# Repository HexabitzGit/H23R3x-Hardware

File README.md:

# H23R3x-Hardware
Hexabitz BlueNRG-M2 Bluetooth Module Hardware Design

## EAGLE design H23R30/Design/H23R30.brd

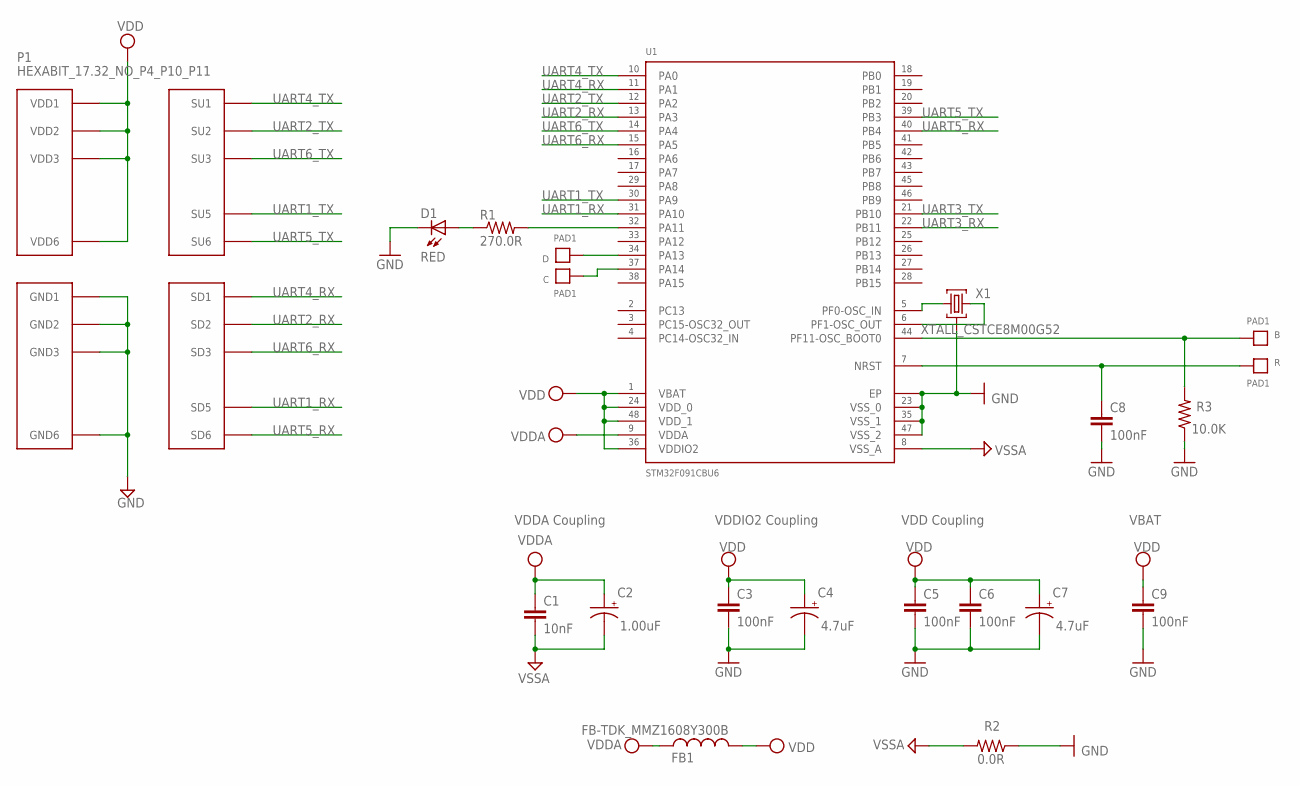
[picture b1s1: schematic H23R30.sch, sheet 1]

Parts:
B: PAD1
C: PAD1
C1: 10nF; C-0603; TOLERANCE 10%; VOLTAGE_RATING 50V; MPN C0603C103K5RACTU
C2: 1.00uF; C-0805-POL; TOLERANCE 10%; VOLTAGE_RATING 16V; MPN CC0805KKX7R7BB105
C3, C6, C8: 100nF; C-0603; TOLERANCE 10%; VOLTAGE_RATING 10V; MPN C0603C104K8RACTU
C4, C7: 4.7uF; C-0805-POL; TOLERANCE 10%; VOLTAGE_RATING 25V; MPN GRM21BC81E475KA12L
C5: 100nF; C-0603; TOLERANCE 10%; VOLTAGE_RATING 10; MPN C0603C104K8RACTU
C9: 100nF; C-0603; TOLERANCE 10V; VOLTAGE_RATING 10%; MPN C0603C104K8RACTU
D: PAD1
D1: RED; VLMS1300-GS08; MPN VLMS1300-GS08
FB1: FB-TDK_MMZ1608Y300B; MPN MMZ1608Y300B
P1: HEXABIT_17.32_NO_P4_P10_P11
R: PAD1
R1: 270.0R; R-0603; TOLERANCE 1%; MPN RC0603FR-07270RL
R2: 0.0R; R-0603; MPN RC0603JR-070RL
R3: 10.0K; R-0603; TOLERANCE 5%; MPN RC0603JR-0710KL
U1: STM32F091CBU6
X1: XTALL_CSTCE8M00G52

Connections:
B1: B.P$1, B.P$2, R3.2, U1.P$44 (PF11-OSC_BOOT0)
GND: C3.2, C4.2 (-), C5.2, C6.2, C7.2 (-), C8.2, C9.2, D1.C, P1.PAD_PD7 (GND1), P1.PAD_PD8 (GND2), P1.PAD_PD9 (GND3), P1.PAD_PD12 (GND6), R2.1, R3.1, U1.EP, U1.P$23 (VSS_0), U1.P$35 (VSS_1), U1.P$47 (VSS_2), X1.P$2 (2); also elsewhere on the board
unnamed: R1.2, U1.P$32 (PA11)
unnamed: D1.A, R1.1
unnamed: U1.P$5 (PF0-OSC_IN), X1.P$1 (1)
unnamed: U1.P$6 (PF1-OSC_OUT), X1.P$3 (3)
unnamed: D.P$1, D.P$2, U1.P$34 (PA13)
unnamed: C.P$1, C.P$2, U1.P$37 (PA14)
R1: C8.1, R.P$1, R.P$2, U1.P$7 (NRST)
UART1_RX: P1.PAD_PD5 (SD5), U1.P$31 (PA10)
UART1_TX: P1.PAD_PU5 (SU5), U1.P$30 (PA9)
UART2_RX: P1.PAD_PD2 (SD2), U1.P$13 (PA3)
UART2_TX: P1.PAD_PU2 (SU2), U1.P$12 (PA2)
UART3_RX: U1.P$22 (PB11); also elsewhere on the board
UART3_TX: U1.P$21 (PB10); also elsewhere on the board
UART4_RX: P1.PAD_PD1 (SD1), U1.P$11 (PA1)
UART4_TX: P1.PAD_PU1 (SU1), U1.P$10 (PA0)
UART5_RX: P1.PAD_PD6 (SD6), U1.P$40 (PB4)
UART5_TX: P1.PAD_PU6 (SU6), U1.P$39 (PB3)
UART6_RX: P1.PAD_PD3 (SD3), U1.P$15 (PA5)
UART6_TX: P1.PAD_PU3 (SU3), U1.P$14 (PA4)
VDD: C3.1, C4.1 (+), C5.1, C6.1, C7.1 (+), C9.1, FB1.2, P1.PAD_PU7 (VDD1), P1.PAD_PU8 (VDD2), P1.PAD_PU9 (VDD3), P1.PAD_PU12 (VDD6), U1.P$1 (VBAT), U1.P$24 (VDD_0), U1.P$36 (VDDIO2), U1.P$48 (VDD_1); also elsewhere on the board
VDDA: C1.1, C2.1 (+), FB1.1, U1.P$9 (VDDA)
VSSA: C1.2, C2.2 (-), R2.2, U1.P$8 (VSS_A)

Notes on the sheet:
VDDA Coupling
VDDIO2 Coupling
VDD Coupling
VBAT

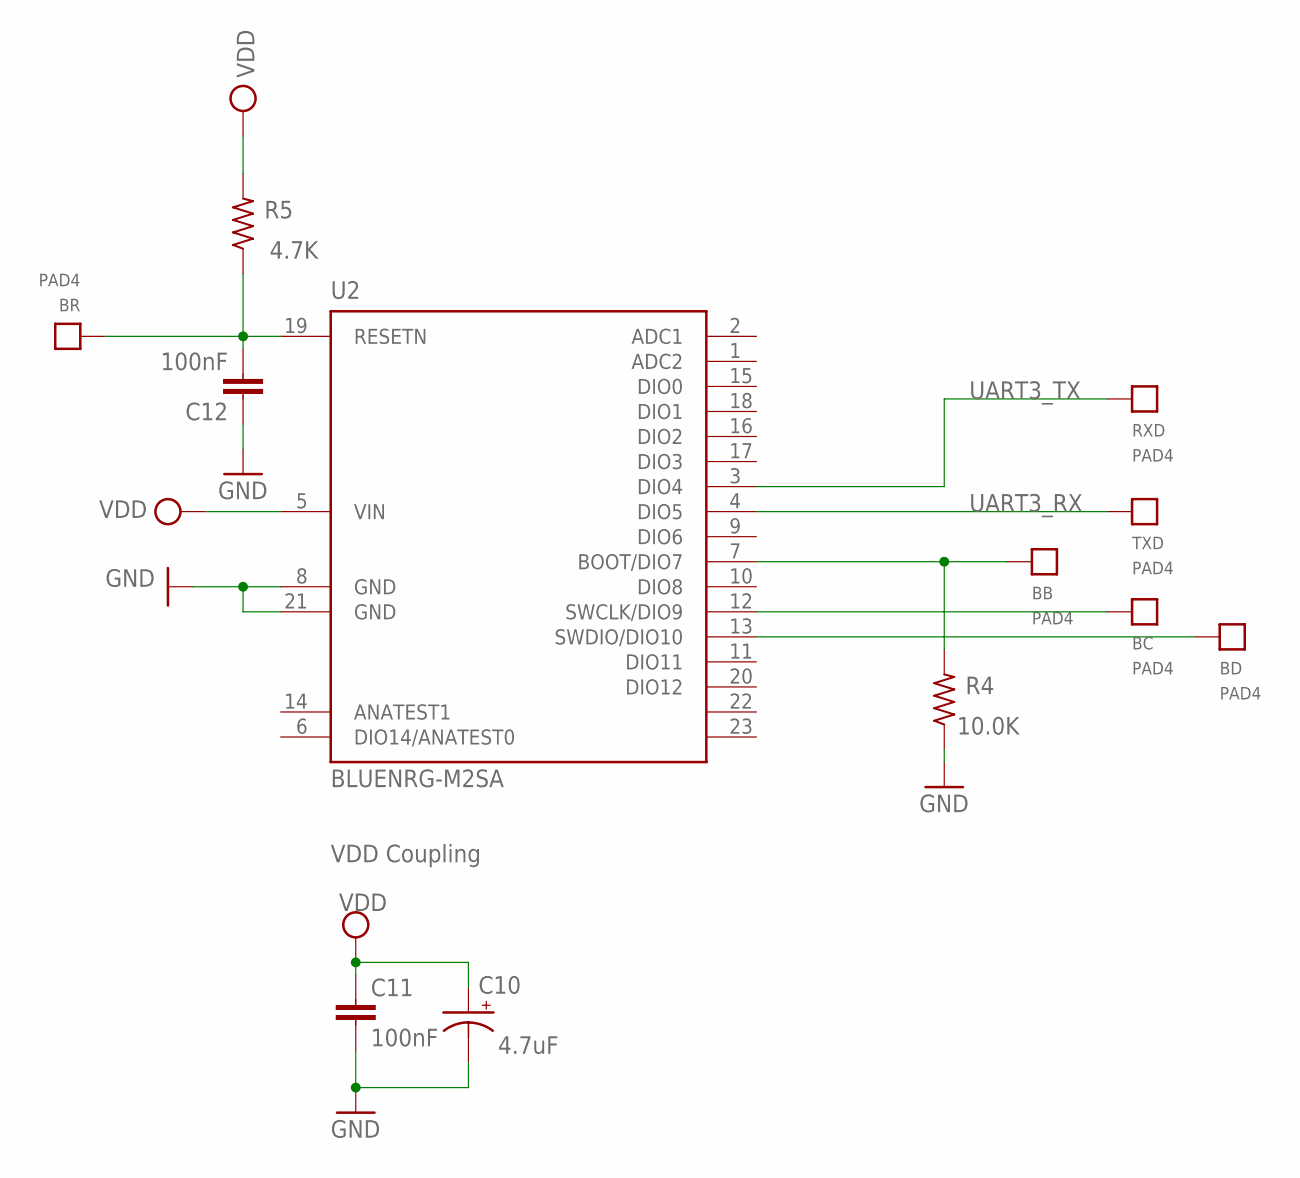
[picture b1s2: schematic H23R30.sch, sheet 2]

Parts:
BB: PAD4
BC: PAD4
BD: PAD4
BR: PAD4
C10: 4.7uF; C-0805-POL; TOLERANCE 10%; VOLTAGE_RATING 25V; MPN GRM21BC81E475KA12L
C11, C12: 100nF; C-0603; TOLERANCE 10%; VOLTAGE_RATING 10; MPN C0603C104K8RACTU
R4: 10.0K; R-0603; TOLERANCE 5%; MPN RC0603JR-0710KL
R5: 4.7K; R-0603; TOLERANCE 5%; MPN RC0603JR-074K7L
RXD: PAD4
TXD: PAD4
U2: BLUENRG-M2SA; BLURNGR-M2SA_FOOTPRINT

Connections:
B2: BB.P$1, R4.2, U2.7 (BOOT/DIO7)
GND: C10.2 (-), C11.2, C12.1, R4.1, U2.8 (GND), U2.21 (GND); also elsewhere on the board
unnamed: BD.P$1, U2.13 (SWDIO/DIO10)
unnamed: BC.P$1, U2.12 (SWCLK/DIO9)
unnamed: BR.P$1, C12.2, R5.1, U2.19 (RESETN)
UART3_RX: TXD.P$1, U2.4 (DIO5); also elsewhere on the board
UART3_TX: RXD.P$1, U2.3 (DIO4); also elsewhere on the board
VDD: C10.1 (+), C11.1, R5.2, U2.5 (VIN); also elsewhere on the board

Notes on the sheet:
VDD Coupling

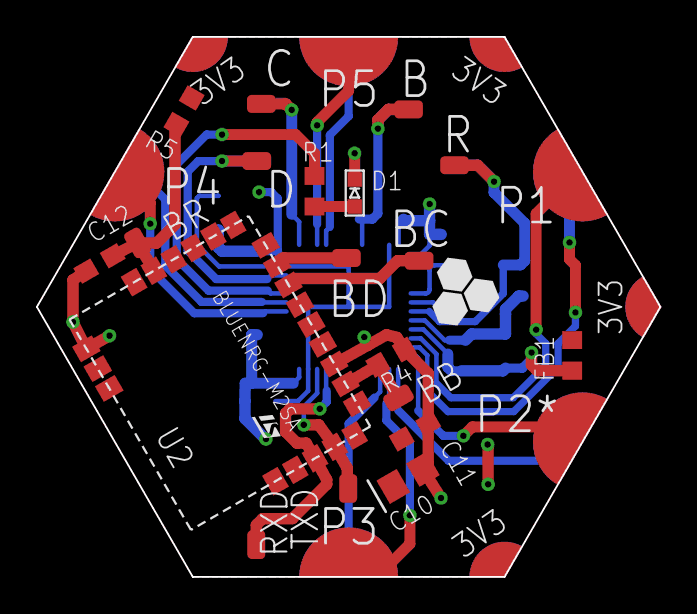
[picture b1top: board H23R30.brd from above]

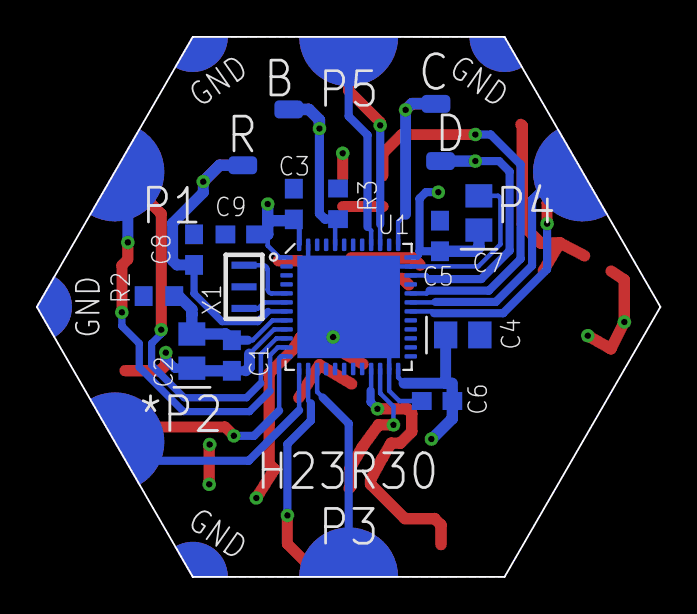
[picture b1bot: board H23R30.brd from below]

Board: 2 copper layers, 34.6 x 30.0 mm, 33 parts (13 on the bottom side), 28 nets.

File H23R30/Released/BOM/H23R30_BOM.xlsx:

Qty | Value | Designator | Description | CAPACITANCE | MFN | MPN | OCTOPART_URL | TOLERANCE
1 | 0.0R | R2 | Thick Film Resistors - SMD 0603 |  | Yageo | RC0603JR-070RL | https://octopart.com/rc0603jr-070rl-yageo-1241539?r=sp&s=X2N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
1 | 270.0R | R1 | Thick Film Resistors - SMD 0603 |  | Yageo | RC0603FR-07270RL | https://octopart.com/search?q=RC0603FR-07270RL&start=0 | 0.01
1 | 4.7K | R5 | Thick Film Resistors - SMD 0603 |  | Yageo | RC0603JR-074K7L | https://octopart.com/rc0603jr-074k7l-yageo-55458509?r=sp | 0.05
2 | 10.0K | R3, R4 | Thick Film Resistors - SMD 0603 |  | Yageo | RC0603JR-0710KL | https://octopart.com/search?q=RC0603JR-0710KL&start=0 | 0.05
1 | 10nF | C1 | CAP CER 10% X7R 0603 | 10nF | KEMET | C0603C103K5RACTU | https://octopart.com/c0603c103k5ractu-kemet-133094?r=sp&s=R_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 | 0.1
7 | 100nF | C5, C11, C12, C3, C6, C8, C9 | CAP CER 10% X7R 0603 | 100nF | KEMET | C0603C104K8RACTU | https://octopart.com/c0603c104k8ractu-kemet-145075?r=sp&s=9b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 | 0.1
1 | 1.00uF | C2 | Cap Tant Solid SMD 2012 | 1.00uF | Yageo | CC0805KKX7R7BB105 | https://octopart.com/cc0805kkx7r7bb105-yageo-8376555?r=sp&s=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 | 0.1
3 | 4.7uF | C4, C7, C10 | Cap Tant Solid SMD 2012 | 4.7uF | Murata | GRM21BC81E475KA12L | https://octopart.com/grm21bc81e475ka12l-murata-10331911?r=sp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 | 0.1
1 | BLUENRG-M2SA | U2 | Embedded ST BlueNRG-2 BLE SoC |  | STMicroelectronics | BlueNRG_M2SA | https://octopart.com/bluenrg-m2sa-stmicroelectronics-104772812?r=sp
1 | FB-TDK_MMZ1608Y300B | FB1 | Ferrite Beads Multi-Layer 30Ohm 25% 100MHz 1.5A 50mOhm DCR 0603 |  | TDK | MMZ1608Y300B | https://octopart.com/mmz1608y300b-tdk-368280?r=sp&s=cd9_2ZEq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
4 | PAD1 | B, C, D, R
6 | PAD4 | BB, BC, BD, BR, RXD, TXD
1 | RED | D1 | Red 0603 Clear 54 mcd 2 V Surface Mount ChipLED ; |  | Vishay | VLMS1300-GS08 | https://octopart.com/vlms1300-gs08-vishay-21709201?r=sp&s=_g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
1 | STM32F091CBU6 | U1 | MCU 32-bit ARM Cortex M0 RISC 128KB Flash 2.5V/3.3V 48-Pin UFQFPN |  | STMicroelectronics | STM32F091CBU6 | https://octopart.com/stm32f091cbu6-stmicroelectronics-519886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
1 | XTALL_CSTCE8M00G52 | X1 | MURATA Ceramic Resonator 8MHz ±0.5% (Tol) ±0.2% (Stability) 33pF 40Ohm 3-Pin CS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 |  | Murata | CSTNE8M00G550000R0 | https://octopart.com/cstne8m00g550000r0-murata-91406934?r=sp

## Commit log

2020-07-11 Copying script generated files
2020-07-18 Bluetooth BlueNRG module
2020-07-29 no message
2020-07-29 Relase
2020-07-29 FIX and add 3D Step Model
2021-04-18 Release REV 1
2021-04-18 H23R31 BOM
2021-04-21 Fix To REV0
